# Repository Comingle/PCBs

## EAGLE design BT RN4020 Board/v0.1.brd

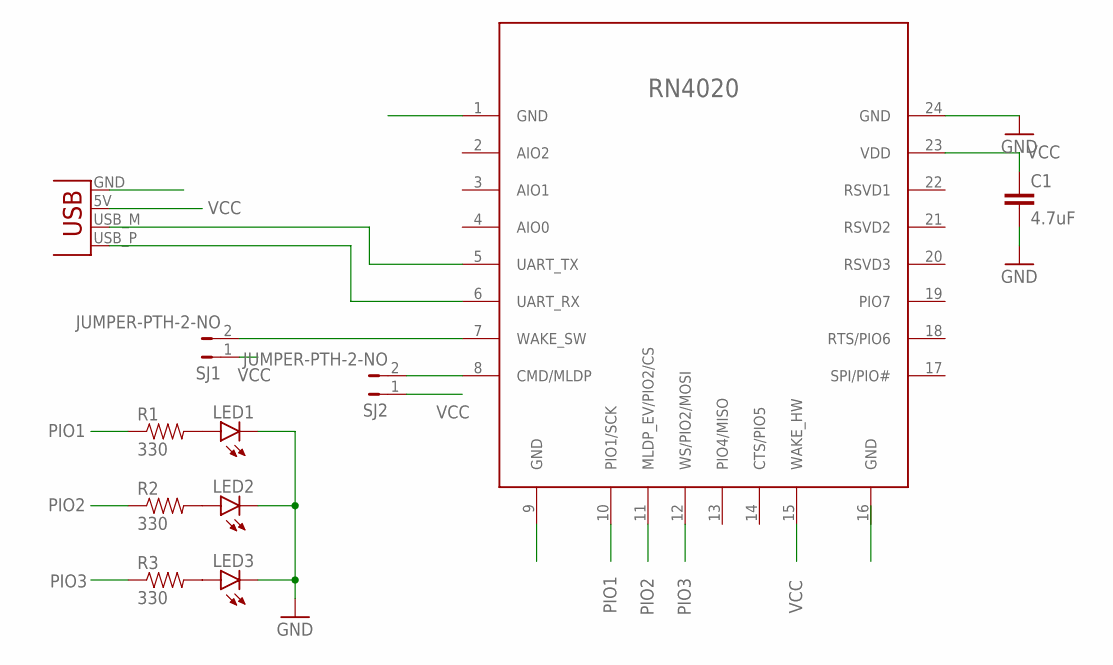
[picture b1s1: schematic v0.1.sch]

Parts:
C1: 4.7uF; 1206
JP1: USBPCB; USB-A-PCB
LED1, LED2, LED3: LED1206; LED-1206
R1, R2, R3: 330; 0603-RES
SJ1, SJ2: JUMPER-PTH-2-NO; PTH-JUMPER-2-NO_NO_SILK
U$1: RN4020

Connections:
GND: C1.2, JP1.GND, LED1.C, LED2.C, LED3.C, U$1.1 (GND), U$1.9 (GND), U$1.16 (GND), U$1.24 (GND)
unnamed: LED1.A, R1.2
unnamed: JP1.USB_M (D-), U$1.5 (UART_TX)
unnamed: JP1.USB_P (D+), U$1.6 (UART_RX)
unnamed: SJ2.2, U$1.8 (CMD/MLDP)
unnamed: LED2.A, R2.2
unnamed: LED3.A, R3.2
unnamed: SJ1.2, U$1.7 (WAKE_SW)
PIO1: R1.1, U$1.10 (PIO1/SCK)
PIO2: R2.1, U$1.11 (MLDP_EV/PIO2/CS)
PIO3: R3.1, U$1.12 (WS/PIO2/MOSI)
VCC: C1.1, JP1.5V (VBUS), SJ1.1, SJ2.1, U$1.15 (WAKE_HW), U$1.23 (VDD)

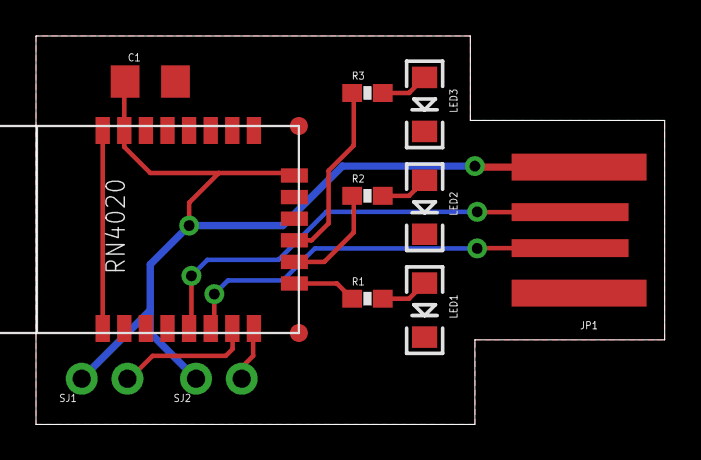
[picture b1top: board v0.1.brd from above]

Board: 2 copper layers, 34.9 x 21.6 mm, 11 parts (0 on the bottom side), 12 nets.

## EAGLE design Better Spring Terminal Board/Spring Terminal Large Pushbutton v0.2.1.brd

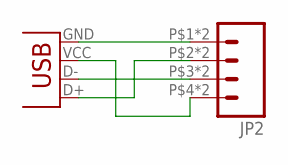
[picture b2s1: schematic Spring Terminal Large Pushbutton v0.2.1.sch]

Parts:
JP1: USBMICROB-GCT-USB3075; USB-MICROB-GCT-USB3075
JP2: M04LARGE_PUSHBTN_SPRING_TERM; 1X04_LARGE_PUSHBTN_SPRING_TERM

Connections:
3V3: JP1.VCC (VBUS), JP2.P$4 (4), JP2.P$5 (4)
D+: JP1.D+, JP2.P$2 (2), JP2.P$7 (2)
D-: JP1.D-, JP2.P$3 (3), JP2.P$6 (3)
GND: JP1.GND, JP2.P$1 (1), JP2.P$8 (1)

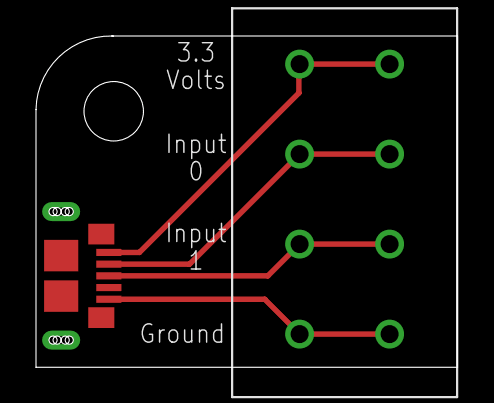
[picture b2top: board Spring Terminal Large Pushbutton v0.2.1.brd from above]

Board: 2 copper layers, 23.4 x 18.4 mm, 3 parts (0 on the bottom side), 4 nets.

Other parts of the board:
U$1: STAND-OFF

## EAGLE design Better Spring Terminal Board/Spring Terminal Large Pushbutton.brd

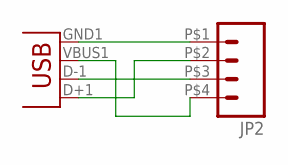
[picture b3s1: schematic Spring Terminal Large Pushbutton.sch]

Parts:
JP1: USB; USB-B-MICRO-SMD_V03
JP2: M04LARGE_PUSHBTN_SPRING_TERM; 1X04_LARGE_PUSHBTN_SPRING_TERM

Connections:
3V3: JP1.VBUS1 (VBUS), JP2.P$4 (4)
D+: JP1.D+1 (D+), JP2.P$2 (2)
D-: JP1.D-1 (D-), JP2.P$3 (3)
GND: JP1.GND1 (GND), JP2.P$1 (1)

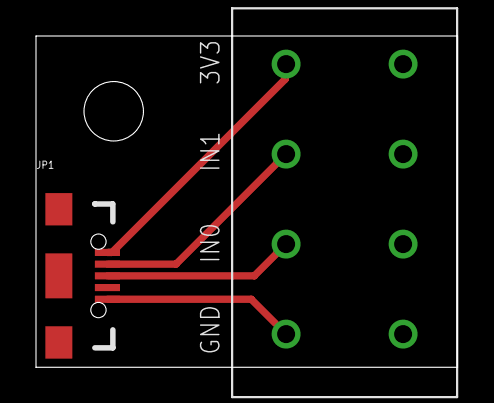
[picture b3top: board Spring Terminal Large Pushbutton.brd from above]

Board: 2 copper layers, 23.4 x 18.4 mm, 3 parts (0 on the bottom side), 4 nets.

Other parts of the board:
U$1: STAND-OFF

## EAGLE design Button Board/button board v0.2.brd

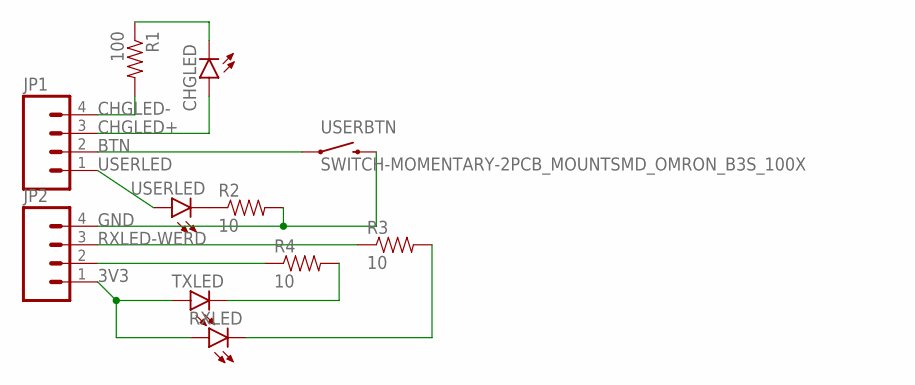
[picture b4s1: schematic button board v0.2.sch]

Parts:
CHGLED: LED-FKIT-1206; FKIT-LED-1206
JP1, JP2: M04PTH; 1X04
R1: 100; 0603-RES
R2, R3, R4: 10; 0603-RES
RXLED: LED-FKIT-1206; FKIT-LED-1206
TXLED: LED-FKIT-1206; FKIT-LED-1206
USERBTN: SWITCH-MOMENTARY-2PCB_MOUNTSMD_OMRON_B3S_100X; TACTILE_SWITCH_LARGE
USERLED: LED-FKIT-1206; FKIT-LED-1206

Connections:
3V3: JP2.1, RXLED.A, TXLED.A
BTN: JP1.2, USERBTN.1, USERBTN.2 (1)
CHGLED+: CHGLED.A, JP1.3
CHGLED-: JP1.4, R1.2
GND: JP2.4, R2.2, USERBTN.3 (2), USERBTN.4 (2)
unnamed: CHGLED.C, R1.1
unnamed: R2.1, USERLED.C
RXLED-: JP2.3, R3.1
RXLED-WERD: R3.2, RXLED.C
TXLED-: JP2.2, R4.1
TXLED-WERD: R4.2, TXLED.C
USERLED: JP1.1, USERLED.A

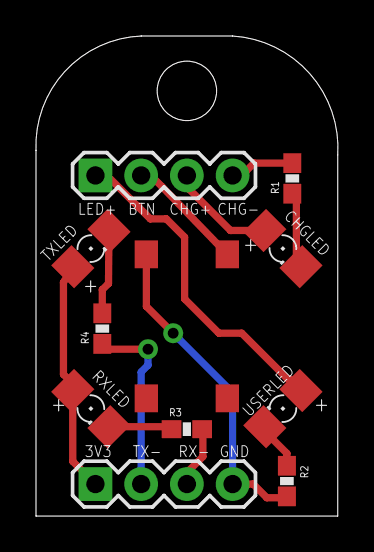
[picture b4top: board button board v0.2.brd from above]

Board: 2 copper layers, 16.8 x 26.7 mm, 12 parts (0 on the bottom side), 12 nets.

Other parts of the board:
U$1: STAND-OFF

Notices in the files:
parts and their libraries:
SparkFun-Connectors: Licensing: Creative Commons ShareAlike 4.0 International - https://creativecommons.org/licenses/by-sa/4.0
